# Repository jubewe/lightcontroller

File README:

--- 1.0 Einleitung ---

  Diese Software wurde von 2 Schülern der Schule / Bühnentechnik geschrieben und ist unter der Gnu General Public License (Version 3) lizenziert (https://www.gnu.org/licenses/gpl-3.0.en.html)

  GitHub Repository: https://github.com/jubewe/lightcontroller
  CAD Case: https://cad.onshape.com/documents/32544a06e8ec4764e1459a3b/w/4d291bb81697a02a01b341a5/e/0fd6ec4ab97829387aade676

--- 1.0.2 Verbindung ---
  Um den Lightcontroller bedienen zu können, verbinde dich per WLAN dem Gerät (am Handy Mobile Daten ausschalten):
  SSID:   lightcontroller
  PW:     password

  Nach erfolgreichem Verbinden, gehe auf http://192.168.4.1.
  Dort findest du das Webinterface für den Controller.

  Beim Abrufen der Seite wird anfangs der aktuelle Status der Lichter abgefragt und synchronisiert

--- 1.1 Gruppen von Lichtern ---

  Namen und Beschreibungen gesehen von Eingang Aula (Pausenhof)
  → Außen = Weiter von Mitte der Aula weg
  → Innen = Näher an Mitte der Aula

Syntax: 
* <Gruppe>: <Beschreibung>

* Bühne: Alle Lichter an Traverse
* Spots: Alle Spots vor der Bühne

* Links: Alle Lichter links der Mitte der Aula (inkl. Spots)
* Rechts: Alle Lichter rechts der Mitte der Aula (inkl. Spots)

# Bühne:
* Bühne Links: Alle Lichter links der Mitte der Traverse
* Bühne Rechts: Alle Lichter rechts der Mitte der Traverse

* Bühne Hinten: Alle Lichter auf hinterer Traverse
* Bühne Vorne: Alle Lichter auf vorderer Traverse

* Bühne Links Außen: Alle Lichter in Äußerster Linker Reihe
* Bühne Links Innen: Alle Lichter in Linker Mittlerer Reihe

* Bühne Rechts Außen: Alle Lichter in Äußerster Rechter Reihe
* Bühne Rechts Innen: Alle Lichter in Rechter Mittlerer Reihe

* Bühne Links Vorne: Alle Vorderen Lichter der Gruppe "Bühne Links"
* Bühne Links Hinten: Alle Hinteren Lichter der Gruppe "Bühne Links"

* Bühne Rechts Vorne: Alle Vorderen Lichter der Gruppe "Bühne Rechts"
* Bühne Rechts Hinten: Alle Hinteren Lichter der Gruppe "Bühne Rechts"

# Spots:
* Spots Links: Alle Spots links der Mitte der Aula
* Spots Rechts: Alle Spots rechts der Mitte der Aula

* Spots Oben: Alle oberen Spots
* Spots Unten: Alle unteren Spots

--- 1.2 DMX-Addressen ---

  Für jeden Scheinwerfer, egal ob RGB-LED oder nicht, sind je 6 Kanäle reserviert (für Kompatibilität von neuen LED Scheinwerfern)

  Da das DMX-Protokoll genutzt wird, kann jedem Kanal ein Wert von 0 bis 255 zugewiesen werden

  # Kanalbelegung der Kanäle (Normal): 
    dimm,0,0,0,0,0

  # Kanalbelegung der Kanäle (LED): 
  # → Werte der Kanäle der LEDs werden von der Website gedimmt
    rot,grün,blau,weiß,bernstein,uv

--- 1.2.2 Belegung der DMX-Addressen ---

Syntax: 
* <name>                   <dmx start>   <dmx end>

* Bühne Links Außen Hinten         1       6
* Bühne Links Innen Hinten         7       12
* Bühne Rechts Innen Hinten        13      18
* Bühne Rechts Außen Hinten        19      24
* Bühne Links Außen Vorne          25      30
* Bühne Links Innen Vorne          31      36
* Bühne Rechts Innen Vorne         37      42
* Bühne Rechts Außen Vorne         43      48

* Spot Links Oben                  49      54
* Spot Links Unten                 55      60
* Spot Rechts Oben                 61      66
* Spot Rechts Unten                67      72

--- 1.3 Presets ---

Es besteht die Möglichkeit, lokale Presets zu erstellen, die die Werte der Kanäle speichern.
Dies kann genutzt werden, um schnell zwischen Bühnenbildern (wie Rede und Musik) zu wechseln.
Sie werden aber nur lokal auf dem aktuellen Gerät gespeichert, können aber exportiert werden.
Wichtig: Keine Leerzeichen in Presetnamen!

--- 1.3.1 Speicherung der Presets ---

Format:
<dmx-start>,<r>,<g>,<b>,<w>,<a>,<u>,<dimm>,<fade>

--- 1.4 Known Bugs ---

- Der "flash" Effekt funktioniert nicht
- fade ist teilweise nicht stable -> reconnect oder restart
- DMX Output ist langsam/Latenz (evtl. neu flashen mit kleinerer "maxLights" Variable)

--- 1.5 Flashen der Controller (neue Firmware) ---

- mit VisualStudioCode und Platform.io Extension mit angepasster DMX-library
- Ordner "backend" für master (1x) aktuell hinten links über der Bühne (Leiter und langes USB-C <-> USB-A Kabel)
- Ordner "backend-receiver" für beliebig viele receiver Module (neue MAC Addressen müssen im master code für die Verbindung mit ESP-Now eingetragen werden)
- BOOT Button halten während USB-Eingesteckt wird (manchmal notwendig)

--- 1.6 Notizen zur Hardware/PCB ---

- Schaltplan und PCB-Layout in diesem git-repo (pcb Ordner)
- gerber Dateien für Nachbestellung bei jlcpcb unter "pcb/gerbers_REV1.1/gerbers.zip")
- das Quartz (Y1) und die beiden Kondensatoren (C12,C13) sowie R16 und R17 werden nicht benötigt
- genau Teileliste "parts.ods" mit Bestellnummern für LCSC

--- x.1 Sonstiges ---

Die Website frägt am Anfang den aktuellen Status der Lichter vom Master ab, die Werte überschreiben dann die aktuellen Werte

Arduino Lib espdmx:  https://github.com/Rickgg/ESP-Dmx
→ Example:  https://github.com/Rickgg/ESP-Dmx/blob/master/examples/RGB_DMX/RGB_DMX.ino#L10 

DMX Addresses:  https://www.thedmxwiki.com/dmx_basics/dmx_addresses

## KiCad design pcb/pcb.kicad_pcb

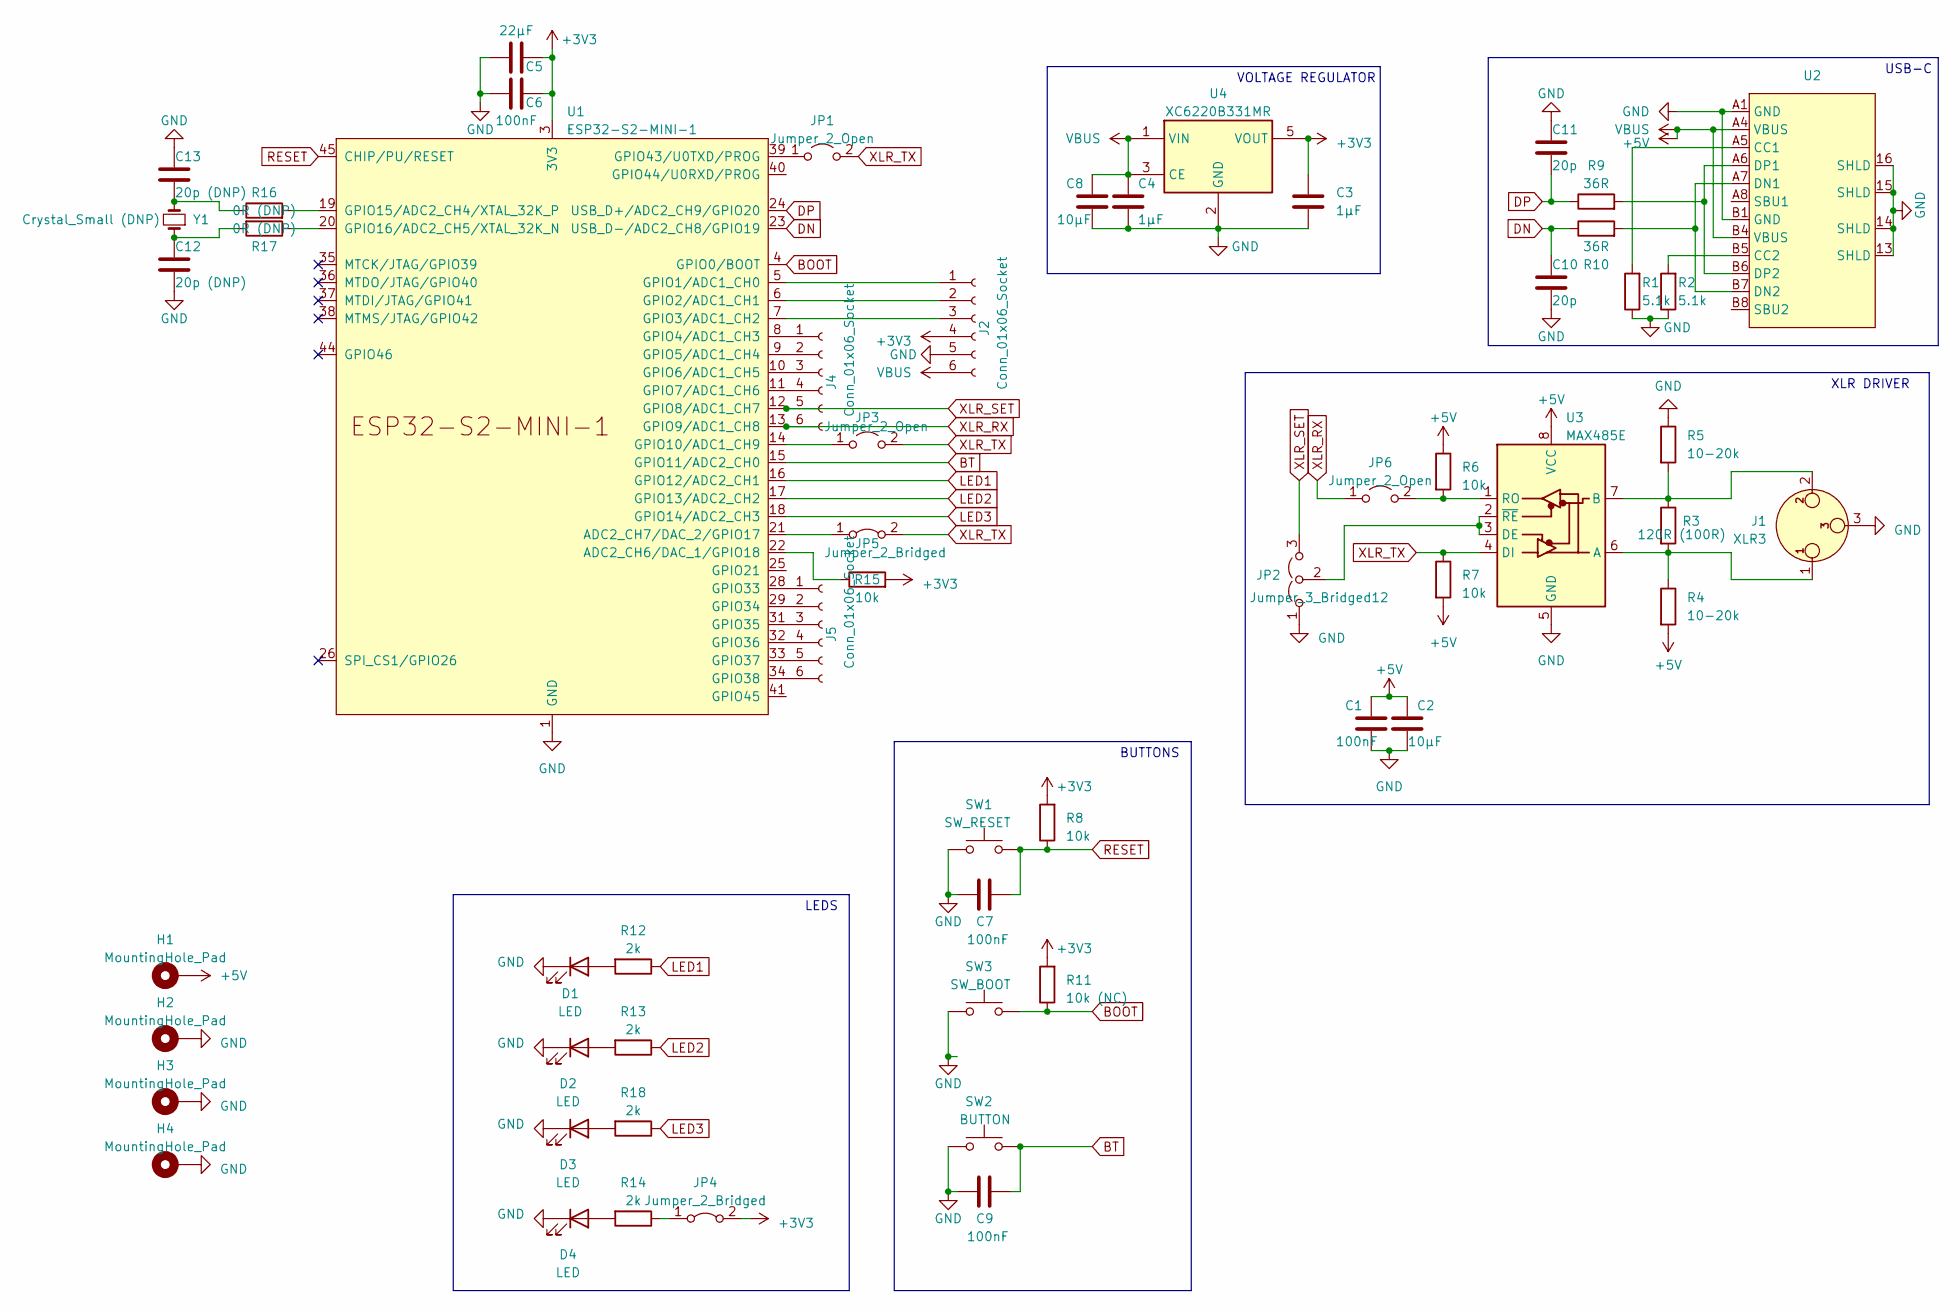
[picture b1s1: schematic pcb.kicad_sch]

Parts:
C1, C6, C7, C9: 100nF; C_0805_2012Metric
C2, C8: 10µF; C_0805_2012Metric
C3, C4: 1µF; C_0805_2012Metric
C5: 22µF; C_0805_2012Metric
C10, C11: 20p; C_0805_2012Metric
C12, C13: 20p (DNP); C_0805_2012Metric
D1, D2, D3, D4: LED; LED_0805_2012Metric
H1, H2, H3, H4: MountingHole_Pad; MountingHole_2.2mm_M2_DIN965_Pad_TopBottom
J1: XLR3; PinHeader_1x03_P2.54mm_Vertical
J2: Conn_01x06_Socket; PinSocket_1x06_P1.27mm_Vertical
J4, J5: Conn_01x06_Socket; PinHeader_1x06_P1.27mm_Vertical
JP1, JP3, JP6: Jumper_2_Open; SolderJumper-2_P1.3mm_Open_RoundedPad1.0x1.5mm
JP2: Jumper_3_Bridged12; SolderJumper-3_P1.3mm_Open_RoundedPad1.0x1.5mm
JP4, JP5: Jumper_2_Bridged; SolderJumper-2_P1.3mm_Bridged_RoundedPad1.0x1.5mm
R1, R2: 5.1k; R_0805_2012Metric
R3: 120R (100R); R_0805_2012Metric
R4, R5: 10-20k; R_0805_2012Metric
R6, R7, R8, R15: 10k; R_0805_2012Metric
R9, R10: 36R; R_0805_2012Metric
R11: 10k (NC); R_0805_2012Metric
R12, R13, R14, R18: 2k; R_0805_2012Metric
R16, R17: 0R (DNP); R_0805_2012Metric
SW1: SW_RESET; SW_SPST_B3U-1000P-B
SW2: BUTTON; SW_SPST_B3U-1000P-B
SW3: SW_BOOT; SW_SPST_B3U-1000P-B
U1: ESP32-S2-MINI-1
U2: XUNPU_TYPEC-304J-BCP16; XUNPU TYPEC-304J-BCP16
U3: MAX485E; SOIC-8_3.9x4.9mm_P1.27mm
U4: XC6220B331MR; SOT-23-5
Y1: Crystal_Small (DNP); Crystal_SMD_3215-2Pin_3.2x1.5mm

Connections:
+3V3: C3.1, C5.2, C6.2, J2.4, JP4.2 (B), R8.2, R11.2, R15.2, U1.3 (3V3), U4.5 (VOUT)
+5V: C1.1, C2.1, C4.1, C8.1, H1.1, J2.6, R4.2, R6.1, R7.2, U2.A4 (VBUS), U2.B4 (VBUS), U3.8 (VCC), U4.1 (VIN), U4.3 (CE)
DN: C10.1, R10.1, U1.23 (USB_D-/ADC2_CH8/GPIO19)
DP: C11.2, R9.1, U1.24 (USB_D+/ADC2_CH9/GPIO20)
GND: C1.2, C2.2, C3.2, C4.2, C5.1, C6.1, C7.2, C8.2, C9.2, C10.2, C11.1, C12.2, C13.1, D1.1 (K), D2.1 (K), D3.1 (K), D4.1 (K), H2.1, H3.1, H4.1, J1.3, J2.5, JP2.1 (A), R1.1, R2.1, R5.1, SW2.1, U1.1 (GND), U1.2 (GND), U1.30 (GND), U1.42 (GND), U1.43 (GND), U1.46 (GND), U1.47 (GND), U1.48 (GND), U1.49 (GND), U1.50 (GND), U1.51 (GND), U1.52 (GND), U1.53 (GND), U1.54 (GND), U1.55 (GND), U1.56 (GND), U1.57 (GND), U1.58 (GND), U1.59 (GND), U1.60 (GND), U1.61 (GND), U1.62 (GND), U1.63 (GND), U1.64 (GND), U1.65 (GND), U2.13 (SHLD), U2.14 (SHLD), U2.15 (SHLD), U2.16 (SHLD), U2.A1 (GND), U2.B1 (GND), U3.5 (GND), U4.2 (GND); also elsewhere on the board
LED1: R12.1, U1.16 (GPIO12/ADC2_CH1)
LED2: R13.1, U1.17 (GPIO13/ADC2_CH2)
LED3: R18.1, U1.18 (GPIO14/ADC2_CH3)
unnamed: C12.1, R17.2, Y1.1
unnamed: C13.2, R16.1, Y1.2
unnamed: D1.2 (A), R12.2
unnamed: D2.2 (A), R13.2
unnamed: D3.2 (A), R18.2
unnamed: D4.2 (A), R14.2
unnamed: J2.1, U1.5 (GPIO1/ADC1_CH0)
unnamed: J2.2, U1.6 (GPIO2/ADC1_CH1)
unnamed: J2.3, U1.7 (GPIO3/ADC1_CH2)
unnamed: J4.1, U1.8 (GPIO4/ADC1_CH3)
unnamed: J4.2, U1.9 (GPIO5/ADC1_CH4)
unnamed: J4.3, U1.10 (GPIO6/ADC1_CH5)
unnamed: J4.4, U1.11 (GPIO7/ADC1_CH6)
unnamed: J5.1, U1.28 (GPIO33)
unnamed: J5.2, U1.29 (GPIO34)
unnamed: J5.3, U1.31 (GPIO35)
unnamed: J5.4, U1.32 (GPIO36)
unnamed: J5.5, U1.33 (GPIO37)
unnamed: J5.6, U1.34 (GPIO38)
unnamed: JP1.1 (A), U1.39 (GPIO43/U0TXD/PROG)
unnamed: JP2.2 (C), U3.2 (~RE), U3.3 (DE)
unnamed: JP3.1 (A), U1.14 (GPIO10/ADC1_CH9)
unnamed: JP4.1 (A), R14.1
unnamed: JP5.1 (A), U1.21 (ADC2_CH7/DAC_2/GPIO17)
unnamed: JP6.2 (B), R6.2, U3.1 (RO)
unnamed: R15.1, U1.22 (ADC2_CH6/DAC_1/GPIO18)
unnamed: R16.2, U1.19 (GPIO15/ADC2_CH4/XTAL_32K_P)
unnamed: R17.1, U1.20 (GPIO16/ADC2_CH5/XTAL_32K_N)
unnamed: R1.2, U2.A5 (CC1)
unnamed: R2.2, U2.B5 (CC2)
unnamed: R10.2, U2.A7 (DN1), U2.B7 (DN2)
unnamed: R9.2, U2.A6 (DP1), U2.B6 (DP2)
unnamed: J1.1, R3.2, R4.1, U3.6 (A)
unnamed: J1.2, R3.1, R5.2, U3.7 (B)
XLR_RX: J4.6, JP6.1 (A), U1.13 (GPIO9/ADC1_CH8)
XLR_SET: J4.5, JP2.3 (B), U1.12 (GPIO8/ADC1_CH7)
XLR_TX: JP1.2 (B), JP3.2 (B), JP5.2 (B), R7.1, U3.4 (DI)

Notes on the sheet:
VOLTAGE REGULATOR
USB-C
LEDS
BUTTONS
XLR DRIVER

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
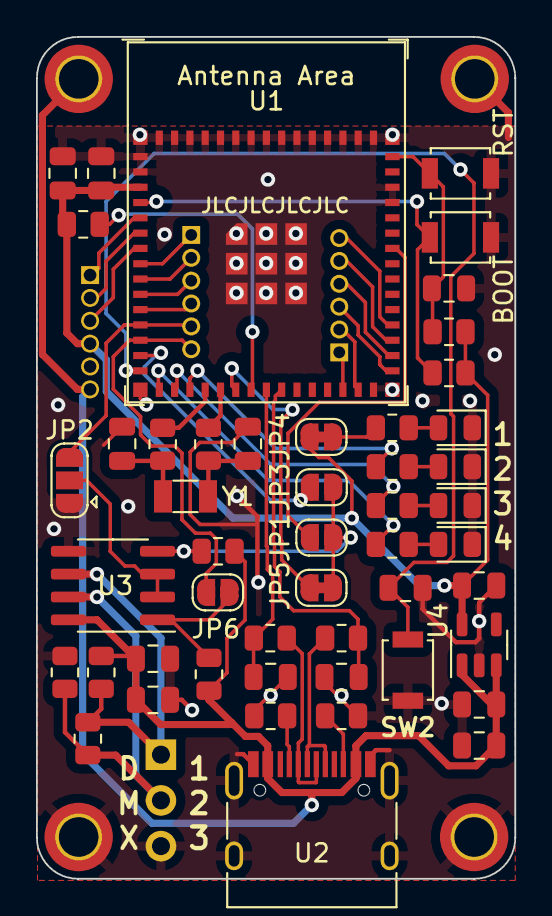
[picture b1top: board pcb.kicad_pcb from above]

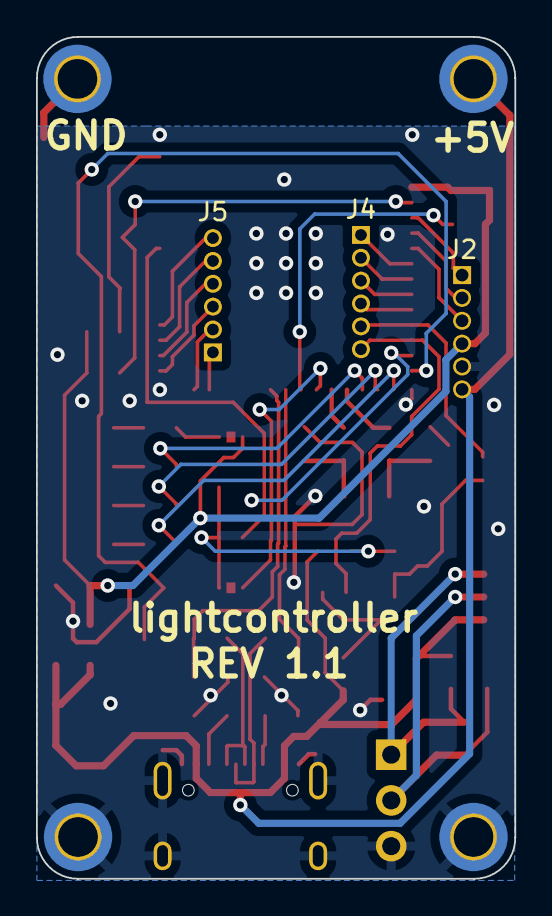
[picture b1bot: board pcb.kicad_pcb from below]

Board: 2 copper layers, 26.6 x 46.8 mm, 57 parts (2 on the bottom side), 48 nets.

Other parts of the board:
BOOT: SW_BOOT; SW_SPST_B3U-1000P-B
RST: SW_RESET; SW_SPST_B3U-1000P-B

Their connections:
GND: BOOT.1, RST.1; also elsewhere on the board

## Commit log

2023-05-16 fe-0.0.1
2023-05-16 fe-0.0.2
2023-05-16 fe0.0.3
2023-05-17 fe-0.0.4
2023-05-18 be-0.0.5
2023-05-18 be-0.0.6
2023-05-18 be-0.0.7
2023-05-19 be-0.0.8
2023-05-19 be-0.0.9
2023-05-21 fe-0.1.0
2023-05-21 fe-0.1.1
2023-05-21 fe-0.1.2
2023-05-21 be-0.1.3
2023-05-21 be-0.1.4
2023-05-21 fe-0.1.5
2023-05-22 be-0.1.6
2023-05-22 pcb-0.1.7
2023-05-22 pcb-0.1.8
2023-05-23 pcb-0.1.9
2023-05-25 be-0.1.8
2023-05-25 pcb-0.2.0
2023-05-30 fe-0.2.1
2023-06-10 pcb-0.2.2
2023-06-10 be-0.2.3
2023-06-13 Create LICENSE
2023-06-13 fe-0.2.4
2023-06-14 3d-0.2.5
2023-06-14 pcb-0.2.6
2023-06-14 be-0.2.7
2023-06-14 fe-0.2.8
2023-06-14 fe-0.2.9
2023-06-14 be-0.3.0
2023-06-16 fe-0.3.1
2023-07-02 be-0.3.2
2023-07-03 be-0.3.3
2023-07-03 fe-0.3.4
2023-07-03 fe-0.3.5
2023-07-04 be-0.3.6
2023-07-06 be-0.3.7
2023-07-06 be-0.3.8
2023-07-06 fe-0.3.9
2023-07-06 fe-0.4.0
2023-07-06 be-0.4.1
2023-07-06 be-0.4.2
2023-07-12 fe-0.4.3
2023-07-12 fe-0.4.4
2023-07-12 be-0.4.5
2023-07-19 be-0.4.6
2023-07-19 fe-0.4.7
